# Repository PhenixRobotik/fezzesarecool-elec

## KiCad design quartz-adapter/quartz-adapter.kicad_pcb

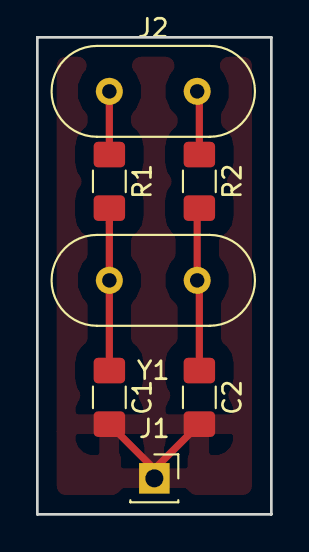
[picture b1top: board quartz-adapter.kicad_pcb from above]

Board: 2 copper layers, 13.0 x 26.5 mm, 7 parts (0 on the bottom side), 5 nets.

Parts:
C1, C2: C; C_1206_3216Metric_Pad1.42x1.75mm_HandSolder
J1: GND; PinSocket_1x01_P2.54mm_Vertical
J2: Conn_01x02; Crystal_HC49-U_Vertical
R1, R2: R; R_1206_3216Metric_Pad1.42x1.75mm_HandSolder
Y1: Crystal; Crystal_HC49-U_Vertical

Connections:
unnamed: C1.1, R1.2, Y1.1
unnamed: C1.2, C2.2, J1.1
unnamed: C2.1, R2.2, Y1.2
unnamed: J2.1, R1.1
unnamed: J2.2, R2.1

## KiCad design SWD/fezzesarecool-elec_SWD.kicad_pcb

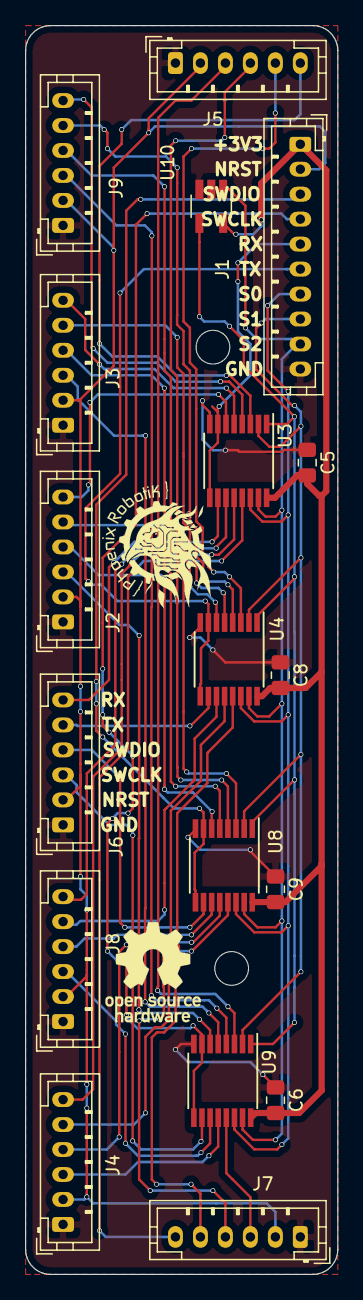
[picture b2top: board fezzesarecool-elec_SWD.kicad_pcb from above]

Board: 2 copper layers, 25.0 x 100.0 mm, 23 parts (1 on the bottom side), 43 nets.

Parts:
C5, C6, C8, C9: C; C_0805_2012Metric_Pad1.15x1.40mm_HandSolder
H1, H2: MountingHole; MountingHole_2.7mm_M2.5
J1: Conn_01x10; JST_PH_B10B-PH-K_1x10_P2.00mm_Vertical
J2, J3, J4, J5, J6, J7, J8, J9: Conn_Debug; JST_PH_B6B-PH-K_1x06_P2.00mm_Vertical
LOGO1: Logo_Open_Hardware_Small; Logo_12,7mm
LOGO2: Logo_Open_Hardware_Small; OSHW-Logo_7.5x8mm_SilkScreen
LOGO3: Logo_Open_Hardware_Small; KiCad-Logo2_8mm_SilkScreen
U3, U4, U8, U9: SN74CB3Q3257; TSSOP-16_4.4x5mm_P0.65mm
U10: SN74LVC1G00; SOT-23-5_HandSoldering

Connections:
+3V3: C5.2, C6.2, C8.2, C9.2, J1.1, U3.16, U4.16, U8.16, U9.16, U10.5
/SWD/RX: J1.5, U3.7, U3.9
/SWD/SWCLK: J1.4, U9.7, U9.9
/SWD/SWDIO: J1.3, U8.7, U8.9
/SWD/TX: J1.6, U4.7, U4.9
/SWD/nrst: J1.2, J2.2, J3.2, J4.2, J5.2, J6.2, J7.2, J8.2, J9.2
/SWD/s0: J1.7, U3.14, U4.14, U8.14, U9.14
/SWD/s1: J1.8, U3.2, U4.2, U8.2, U9.2
/SWD/s2: J1.9, U3.15, U4.15, U8.15, U9.15, U10.1, U10.2
/SWD/~s2: U3.1, U4.1, U8.1, U9.1, U10.4
GND: C5.1, C6.1, C8.1, C9.1, J1.10, J2.1, J3.1, J4.1, J5.1, J6.1, J7.1, J8.1, J9.1, U3.8, U4.8, U8.8, U9.8, U10.3
unnamed: J2.3, U9.6
unnamed: J2.4, U8.6
unnamed: J2.5, U4.6
unnamed: J2.6, U3.6
unnamed: J3.3, U9.5
unnamed: J3.4, U8.5
unnamed: J3.5, U4.5
unnamed: J3.6, U3.5
unnamed: J4.3, U9.12
unnamed: J4.4, U8.12
unnamed: J4.5, U4.12
unnamed: J4.6, U3.12
unnamed: J5.3, U9.3
unnamed: J5.4, U8.3
unnamed: J5.5, U4.3
unnamed: J5.6, U3.3
unnamed: J6.3, U9.10
unnamed: J6.4, U8.10
unnamed: J6.5, U4.10
unnamed: J6.6, U3.10
unnamed: J7.3, U9.13
unnamed: J7.4, U8.13
unnamed: J7.5, U4.13
unnamed: J7.6, U3.13
unnamed: J8.3, U9.11
unnamed: J8.4, U8.11
unnamed: J8.5, U4.11
unnamed: J8.6, U3.11
unnamed: J9.3, U9.4
unnamed: J9.4, U8.4
unnamed: J9.5, U4.4
unnamed: J9.6, U3.4

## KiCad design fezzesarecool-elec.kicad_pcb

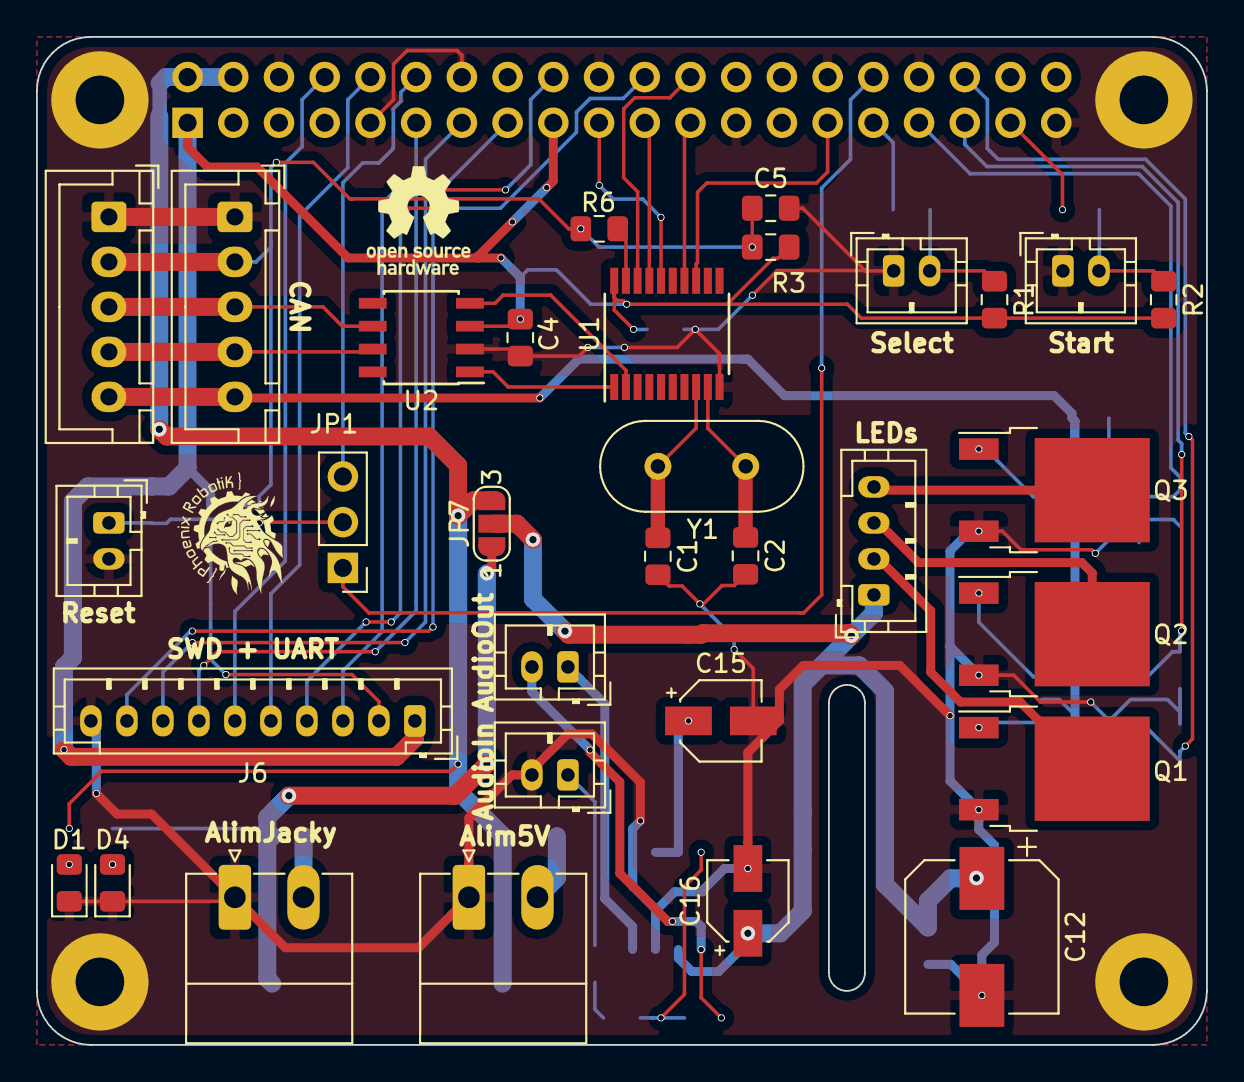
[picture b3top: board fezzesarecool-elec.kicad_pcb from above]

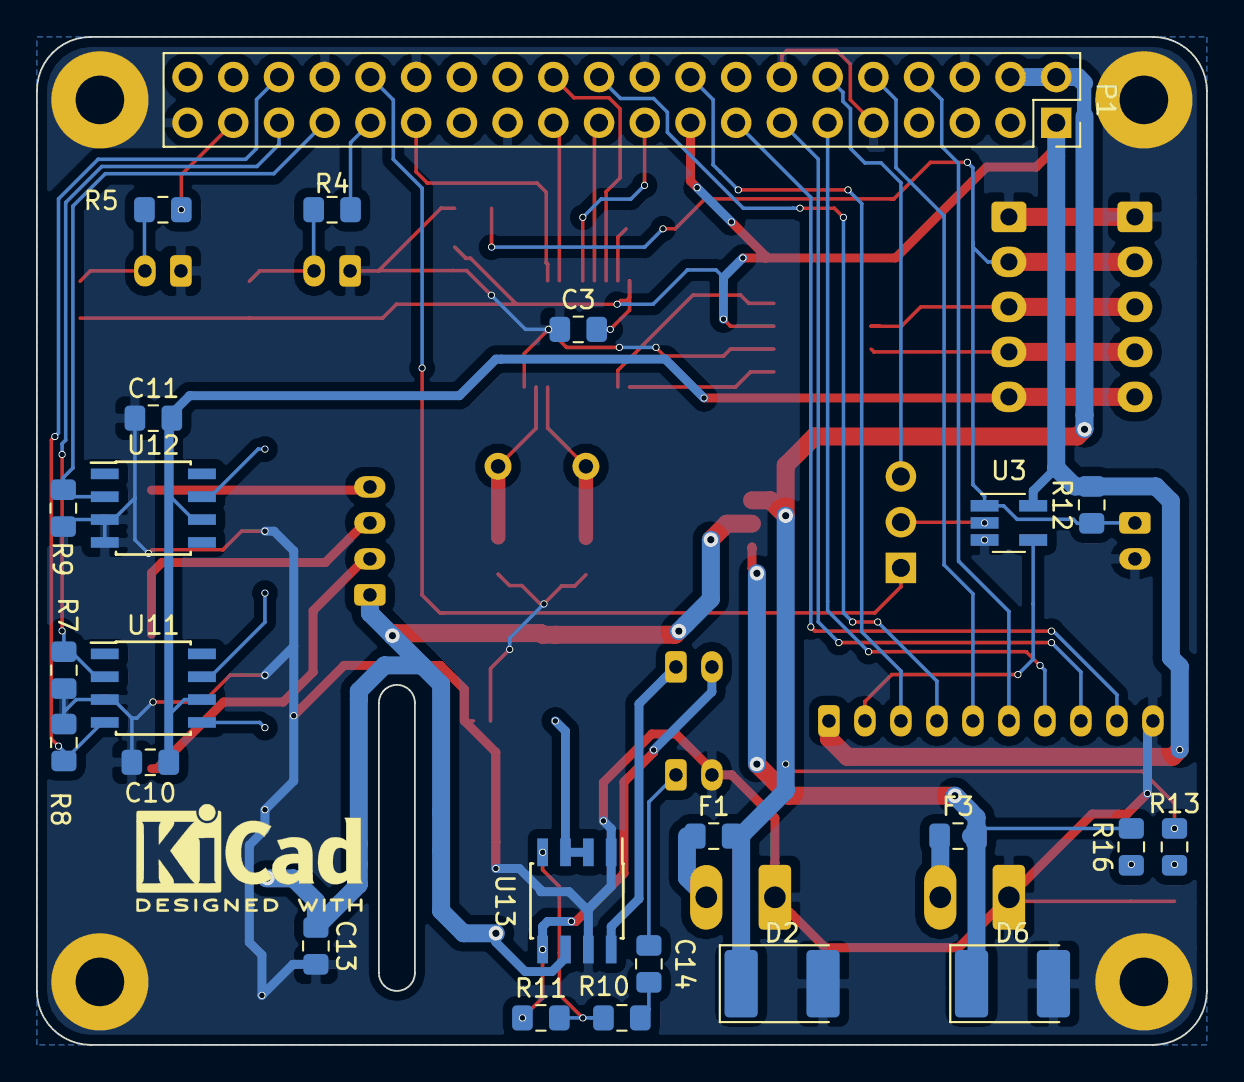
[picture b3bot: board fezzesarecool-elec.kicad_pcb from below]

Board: 2 copper layers, 65.0 x 56.0 mm, 63 parts (25 on the bottom side), 53 nets.

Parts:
C1, C2: 26p; C_0805_2012Metric_Pad1.15x1.40mm_HandSolder
C3, C4, C10, C11, C13: 100n; C_0805_2012Metric_Pad1.15x1.40mm_HandSolder
C5: cf. doc p55; C_0805_2012Metric_Pad1.15x1.40mm_HandSolder
C12: 10µ; CP_Elec_8x10
C14: 0,39u; C_0805_2012Metric_Pad1.15x1.40mm_HandSolder
C15, C16: 1u; CP_Elec_4x5.4
D1, D4: LED; LED_0805_2012Metric_Pad1.15x1.40mm_HandSolder
D2, D6: D; D_2114_3652Metric_Pad1.85x3.75mm_HandSolder
F1, F3: Fuse; Fuse_0805_2012Metric_Pad1.15x1.40mm_HandSolder
H1, H2, H3, H4: MountingHole_Pad; MountingHole_2.7mm_M2.5_Pad
J1: Conn_sel; JST_PH_B2B-PH-K_1x02_P2.00mm_Vertical
J2: Conn_start; JST_PH_B2B-PH-K_1x02_P2.00mm_Vertical
J3, J4: CAN_conn; JST_XH_B05B-XH-A_1x05_P2.50mm_Vertical
J5: Conn_01x02; JST_PH_B2B-PH-K_1x02_P2.00mm_Vertical
J6: Conn_01x10; JST_PH_B10B-PH-K_1x10_P2.00mm_Vertical
J7: alim_5V; PhoenixContact_MC_1,5_2-G-3.81_1x02_P3.81mm_Horizontal
J14: Conn_LEDs; JST_PH_B4B-PH-K_1x04_P2.00mm_Vertical
J15: Audio_input; JST_PH_B2B-PH-K_1x02_P2.00mm_Vertical
J18: alim_jacky; PhoenixContact_MC_1,5_2-G-3.81_1x02_P3.81mm_Horizontal
JP1: reset_method; PinHeader_1x03_P2.54mm_Vertical
JP7: Jumper_NC_Dual; SolderJumper-3_P1.3mm_Open_RoundedPad1.0x1.5mm_NumberLabels
LOGO1: Logo_Open_Hardware_Small; Logo_8,5mm
LOGO2: Logo_Open_Hardware_Small; OSHW-Logo_5.7x6mm_SilkScreen
LOGO3: Logo_Open_Hardware_Small; KiCad-Logo2_6mm_SilkScreen
LS1: Speaker; JST_PH_B2B-PH-K_1x02_P2.00mm_Vertical
P1: Conn_02x20_Odd_Even; PinSocket_2x20_P2.54mm_Vertical
Q1, Q2, Q3: NMOS-T252; TO-252-2
R1, R2, R3, R4, R5, R6, R7, R8, R9, R12, R13, R16: R; R_0805_2012Metric_Pad1.15x1.40mm_HandSolder
R10, R11: 20k; R_0805_2012Metric_Pad1.15x1.40mm_HandSolder
U1: MCP2515-EST; TSSOP-20_4.4x6.5mm_P0.65mm
U2: TCAN332; SOIC-8_3.9x4.9mm_P1.27mm
U3: SN74AHC1G08; SOT-23-5_HandSoldering
U11, U12: MC34152; SOIC-8_3.9x4.9mm_P1.27mm
U13: LM4991; SOIC-8_3.9x4.9mm_P1.27mm
Y1: Crystal_8MHz; Crystal_HC49-U_Vertical

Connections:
+3V3: C3.2, C4.2, J6.1, P1.1, P1.17, R1.2, R2.2, R3.2, R12.2, U1.20, U2.3, U3.5
+5V: D2.1, F1.2, JP7.3, P1.2, P1.4, R13.1
+5VD: C12.1, C13.1, C16.1, J14.1, JP7.2, U13.6
+7.5V: C10.2, C11.2, J3.5, J4.5, U11.6, U12.6
/GPIO5: P1.29, U1.13
/GPIO6: P1.31, R4.1
/GPIO8(SPI0_CE_N): P1.24, U1.18
/GPIO9(SPI0_MISO): P1.21, U1.17
/GPIO10(SPI0_MOSI): P1.19, U1.16
/GPIO11(SPI0_SCK): P1.23, U1.14
/GPIO12(PWM0): JP1.1, P1.32
/GPIO13(PWM1): P1.33, R9.2, U12.2
/GPIO14(TXD0): J6.6, P1.8
/GPIO15(RXD0): J6.5, P1.10
/GPIO16: P1.36, R8.1, U11.4
/GPIO17(GEN0): J6.7, P1.11
/GPIO18(GEN1)(PWM0): JP1.3, P1.12
/GPIO19(SPI1_MISO): P1.35, R7.2, U11.2
/GPIO22(GEN3): J6.9, P1.15
/GPIO24(GEN5): J6.3, P1.18
/GPIO25(GEN6): J6.4, P1.22
/GPIO26: P1.37, R5.2
/GPIO27(GEN2): J6.8, P1.13
/SWD/GRST: C5.1, J3.2, J4.2, J5.1, R3.1, R6.2, R12.1, U3.1
/SWD/nrst: JP1.2, U3.2
GND: C1.2, C2.2, C3.1, C4.1, C5.2, C10.1, C11.1, C12.2, C13.2, C15.2, C16.2, D1.1, D2.2, D4.1, D6.2, H1.1, H2.1, H3.1, H4.1, J1.1, J2.1, J3.1, J4.1, J5.2, J6.10, J7.1, J15.2, J18.1, P1.6, P1.9, P1.14, P1.20, P1.25, P1.30, P1.34, P1.39, Q1.3, Q2.3, Q3.3, R7.1, R8.2, R9.1, U1.10, U2.2, U3.3, U11.3, U12.3, U12.4, U13.1, U13.7
unnamed: C1.1, U1.8, Y1.1
unnamed: C2.1, U1.9, Y1.2
unnamed: C14.1, R10.2
unnamed: C14.2, J15.1
unnamed: C15.1, U13.2, U13.3
unnamed: D1.2, R13.2
unnamed: D4.2, R16.2
unnamed: D6.1, F3.2, JP7.1, R16.1
unnamed: F1.1, J7.2
unnamed: F3.1, J18.2
unnamed: J1.2, R1.1, R4.2
unnamed: J2.2, R2.1, R5.1
unnamed: J3.3, J4.3, U2.6
unnamed: J3.4, J4.4, U2.7
unnamed: J6.2, U3.4
unnamed: J14.2, Q1.2
unnamed: J14.3, Q2.2
unnamed: J14.4, Q3.2
unnamed: LS1.1, U13.8
unnamed: LS1.2, R11.1, U13.5
unnamed: Q1.1, U11.5
unnamed: Q2.1, U11.7
unnamed: Q3.1, U12.7
unnamed: R6.1, U1.19
unnamed: R10.1, R11.2, U13.4
unnamed: U1.1, U2.1
unnamed: U1.2, U2.4

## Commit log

2018-07-27 Add phenix_kicad submodule
2018-07-27 add subschema
2018-08-07 Update, finished schema for blackmagicprobe
2018-08-08 Small schema fixes. PCB basic placement done, now routing.
2018-08-09 pcb changes
2018-08-09 Add nets to rules
2018-08-09 small schema fixes. All is connected on pcb.
2018-10-08 feezz
2018-10-08 submodule problem solved
2018-10-09 electric circuit
2018-10-09 Updated phenix_kicad submodule
2018-10-10 level conversion
2018-10-13 begin footprint
2018-10-13 missing SWD footprint and audio ampli
2018-10-13 non connexions addes
2018-10-15 ready to route
2018-10-15 RPi placed
2018-10-15 placement
2018-10-15 holes added
2018-10-15 route longer than expected
2018-10-19 multiplexeur moved
2018-10-19 multiplexeur routed
2018-10-19 holes addes
2018-10-20 Fix libraries paths
2018-10-20 connectors reorganised
2018-10-20 check rpi connexions
2018-10-21 CAN transiver changed, redy to route
2018-10-23 routed
2018-10-23 resistors addes
2018-10-24 power tracks corrected
2018-10-25 coins arrondis, fix connecteur
2018-11-01 update gitignore and phenix_kicad
2018-11-01 update sym libs
2018-11-04 serigraphy
2018-11-04 power connector
2018-11-04 moved ref
2018-11-05 add logos, fix phoenix phenix
2018-11-05 fix phenix phoenix, add silk
2018-11-05 cleanup
2018-11-07 Update schematics values
2018-11-07 Changed audio capacitors footprint
2018-11-07 Changed fuse footprint
2018-11-09 some weird changes.
2018-11-12 Rename subboard
2019-03-15 rename connectors
2019-03-17 adapter for quartz modification
2019-05-11 Fix component value
2019-05-14 fix lib version
2019-05-14 fix value
2019-05-14 Fix datasheet urls
2019-05-26 oups
2019-11-07 post-lib update
